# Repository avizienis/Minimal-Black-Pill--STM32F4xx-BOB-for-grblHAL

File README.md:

# Minimal Black Pill (STM32F4xx) BOB for grblHAL 
Single layer breakout board for the popular Black Pill (*NOT Blue Pill*). Features 4 axes, 5V outputs, optoisolated inputs.

Firmware: [grblHAL](https://github.com/terjeio/grblHAL)

The goal of this project was to replace a classical Grbl setup on an Arduino Uno/Nano, with minimal effort and minimal features (which is enough for most hobby machines anyway).
All inputs are mapped to one side of the board, all outputs (except spindle PWM) are on the other. 
This allows for a very clean single sided design and is very suitable milling, UV exposing or even toner transfer methods.
The only critical requirements for manufacturing - minimal separation between traces is 0.2mm.

## Feb 2021 Initial release
  * 4 Axis outputs
  * 10 5V buffered outputs (XYZA step/dir outputs, single source-multiple buffered outputs enable, spindle PWM and enable, mist, flood)  
  * 8 Opto-isolated inputs (mapped to XYZ limits, probe, halt, pause, start, safety door)
  * External supply connectors. Can be powered by USB, external 5V or external 12V-24V (depending on the Vreg). 
  * All I/O done on 3.5mm pitch connectors.

## Notes

### Vreg can be a simple 7805 or as in my implementation (also see images folder) - a tiny DC-DC converter. The latter happily accepts up to 24V input.

### This is only tested on genuine [WeAct Black Pill V3](https://github.com/WeActTC/MiniF4-STM32F4x1).
Other/older versions of the board can have slightly different mappings.
Also I've read that blocking USB power diodes are not present on some older variants of the board.
If so, when using external supply microcontroller's 5V lines should not be connected to the main board.

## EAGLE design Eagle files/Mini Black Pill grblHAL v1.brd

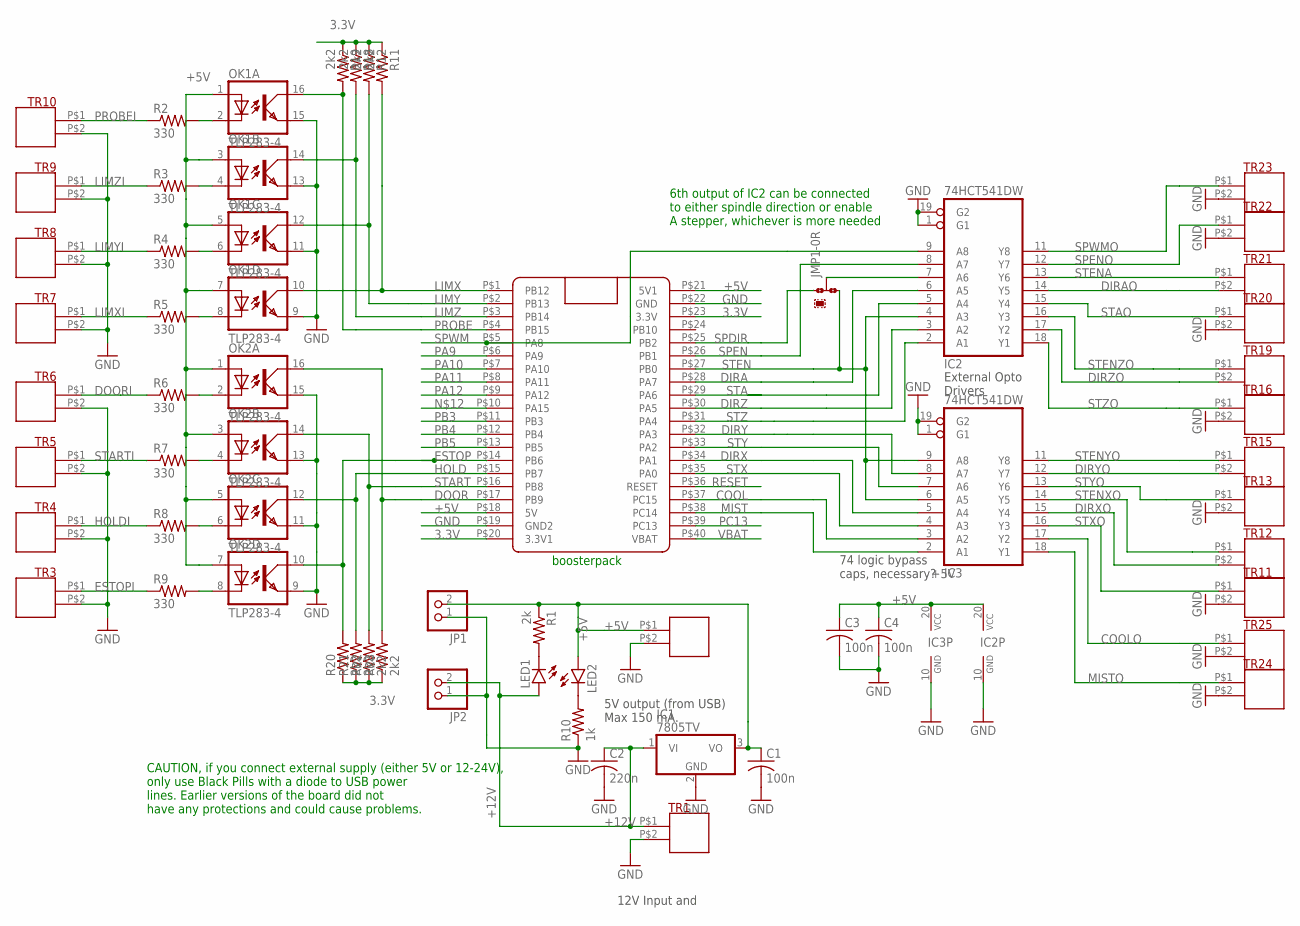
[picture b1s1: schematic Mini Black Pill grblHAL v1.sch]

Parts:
C1, C3, C4: 100n; C0805
C2: 220n; C0805
IC1: 7805TV; TO220V
IC2, IC3: 74HCT541DW; SO20W
JMP1: 0R-JUMPA; A0R-JMP
JP1, JP2: PINHD-1X2; 1X02
LED1, LED2: LED3MM
OK1, OK2: TLP283-4; MINI-FLAT-16
R1: 2k; R0805
R2, R3, R4, R5, R6, R7, R8, R9: 330; R0805
R10: 1k; R0805
R11, R12, R18, R19, R20, R21, R22, R23: 2k2; R0805
TR1, TR2, TR3, TR4, TR5, TR6, TR7, TR8, TR9, TR10, TR11, TR12, TR13, TR15, TR16, TR19, TR20, TR21, TR22, TR23, TR24, TR25: T35-2
U$2: BLACK_PILL; BLUE_PILL

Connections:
3.3V: R11.1, R12.1, R18.1, R19.1, R20.1, R21.1, R22.1, R23.1, U$2.P$20 (3.3V1), U$2.P$23 (3.3V)
+5V: C1.1, C3.1, C4.1, IC1.3 (VO), IC2.20 (VCC), IC3.20 (VCC), JP1.2, LED2.A, OK1.1 (A), OK1.3 (A), OK1.5 (A), OK1.7 (A), OK2.1 (A), OK2.3 (A), OK2.5 (A), OK2.7 (A), R1.1, TR2.P$1, U$2.P$18 (5V), U$2.P$21 (5V1)
+12V: C2.1, IC1.1 (VI), JP2.2, LED1.A, TR1.P$1
COOL: IC3.3 (A2), U$2.P$37 (PC15)
COOLO: IC3.17 (Y2), TR25.P$1
DIRA: IC2.6 (A5), U$2.P$28 (PA7)
DIRAO: IC2.14 (Y5), TR21.P$2
DIRX: IC3.5 (A4), U$2.P$34 (PA1)
DIRXO: IC3.15 (Y4), TR12.P$2
DIRY: IC3.8 (A7), U$2.P$32 (PA3)
DIRYO: IC3.12 (Y7), TR15.P$2
DIRZ: IC2.3 (A2), U$2.P$30 (PA5)
DIRZO: IC2.17 (Y2), TR19.P$2
DOOR: OK2.16 (COL), R23.2, U$2.P$17 (PB9)
DOORI: R6.1, TR6.P$1
ESTOP: OK2.10 (COL), R20.2, U$2.P$14 (PB6)
ESTOPI: R9.1, TR3.P$1
GND: C1.2, C2.2, C3.2, C4.2, IC1.2 (GND), IC2.1 (G1), IC2.10 (GND), IC2.19 (G2), IC3.1 (G1), IC3.10 (GND), IC3.19 (G2), JP1.1, JP2.1, OK1.9 (EMIT), OK1.11 (EMIT), OK1.13 (EMIT), OK1.15 (EMIT), OK2.9 (EMIT), OK2.11 (EMIT), OK2.13 (EMIT), OK2.15 (EMIT), R10.1, TR1.P$2, TR2.P$2, TR3.P$2, TR4.P$2, TR5.P$2, TR6.P$2, TR7.P$2, TR8.P$2, TR9.P$2, TR10.P$2, TR11.P$2, TR13.P$2, TR16.P$2, TR20.P$2, TR22.P$2, TR23.P$2, TR24.P$2, TR25.P$2, U$2.P$19 (GND2), U$2.P$22 (GND)
HOLD: OK2.12 (COL), R21.2, U$2.P$15 (PB7)
HOLDI: R8.1, TR4.P$1
LIMX: OK1.10 (COL), R11.2, U$2.P$1 (PB12)
LIMXI: R5.1, TR7.P$1
LIMY: OK1.12 (COL), R12.2, U$2.P$2 (PB13)
LIMYI: R4.1, TR8.P$1
LIMZ: OK1.14 (COL), R18.2, U$2.P$3 (PB14)
LIMZI: R3.1, TR9.P$1
MIST: IC3.2 (A1), U$2.P$38 (PC14)
MISTO: IC3.18 (Y1), TR24.P$1
unnamed: OK2.2 (C), R6.2
unnamed: LED2.K (C), R10.2
unnamed: OK2.4 (C), R7.2
unnamed: LED1.K (C), R1.2
unnamed: OK2.6 (C), R8.2
unnamed: OK1.8 (C), R5.2
unnamed: OK1.6 (C), R4.2
unnamed: OK1.4 (C), R3.2
unnamed: OK1.2 (C), R2.2
unnamed: OK2.8 (C), R9.2
unnamed: IC2.7 (A6), JMP1.2
PA9: U$2.P$6 (PA9)
PA10: U$2.P$7 (PA10)
PA11: U$2.P$8 (PA11)
PA12: U$2.P$9 (PA12)
PB3: U$2.P$11 (PB3)
PB4: U$2.P$12 (PB4)
PB5: U$2.P$13 (PB5)
PC13: U$2.P$39 (PC13)
PROBE: OK1.16 (COL), R19.2, U$2.P$4 (PB15)
PROBEI: R2.1, TR10.P$1
RESET: U$2.P$36 (RESET)
SPDIR: JMP1.1, U$2.P$25 (PB2)
SPEN: IC2.8 (A7), U$2.P$26 (PB1)
SPENO: IC2.12 (Y7), TR22.P$1
SPWM: IC2.9 (A8), U$2.P$5 (PA8)
SPWMO: IC2.11 (Y8), TR23.P$1
STA: IC2.5 (A4), U$2.P$29 (PA6)
STAO: IC2.15 (Y4), TR20.P$1
START: OK2.14 (COL), R22.2, U$2.P$16 (PB8)
STARTI: R7.1, TR5.P$1
STEN: IC2.4 (A3), IC3.6 (A5), IC3.9 (A8), JMP1.3, U$2.P$27 (PB0)
STENA: IC2.13 (Y6), TR21.P$1
STENXO: IC3.14 (Y5), TR12.P$1
STENYO: IC3.11 (Y8), TR15.P$1
STENZO: IC2.16 (Y3), TR19.P$1
STX: IC3.4 (A3), U$2.P$35 (PA0)
STXO: IC3.16 (Y3), TR11.P$1
STY: IC3.7 (A6), U$2.P$33 (PA2)
STYO: IC3.13 (Y6), TR13.P$1
STZ: IC2.2 (A1), U$2.P$31 (PA4)
STZO: IC2.18 (Y1), TR16.P$1
VBAT: U$2.P$40 (VBAT)

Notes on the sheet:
External Opto Drivers
74 logic bypass caps, necessary?
boosterpack
5V output (from USB) Max 150 mA.
12V Input and
6th output of IC2 can be connected to either spindle direction or enable A stepper, whichever is more needed
CAUTION, if you connect external supply (either 5V or 12-24V), only use Black Pills with a diode to USB power lines. Earlier versions of the board did not have any protections and could cause problems.

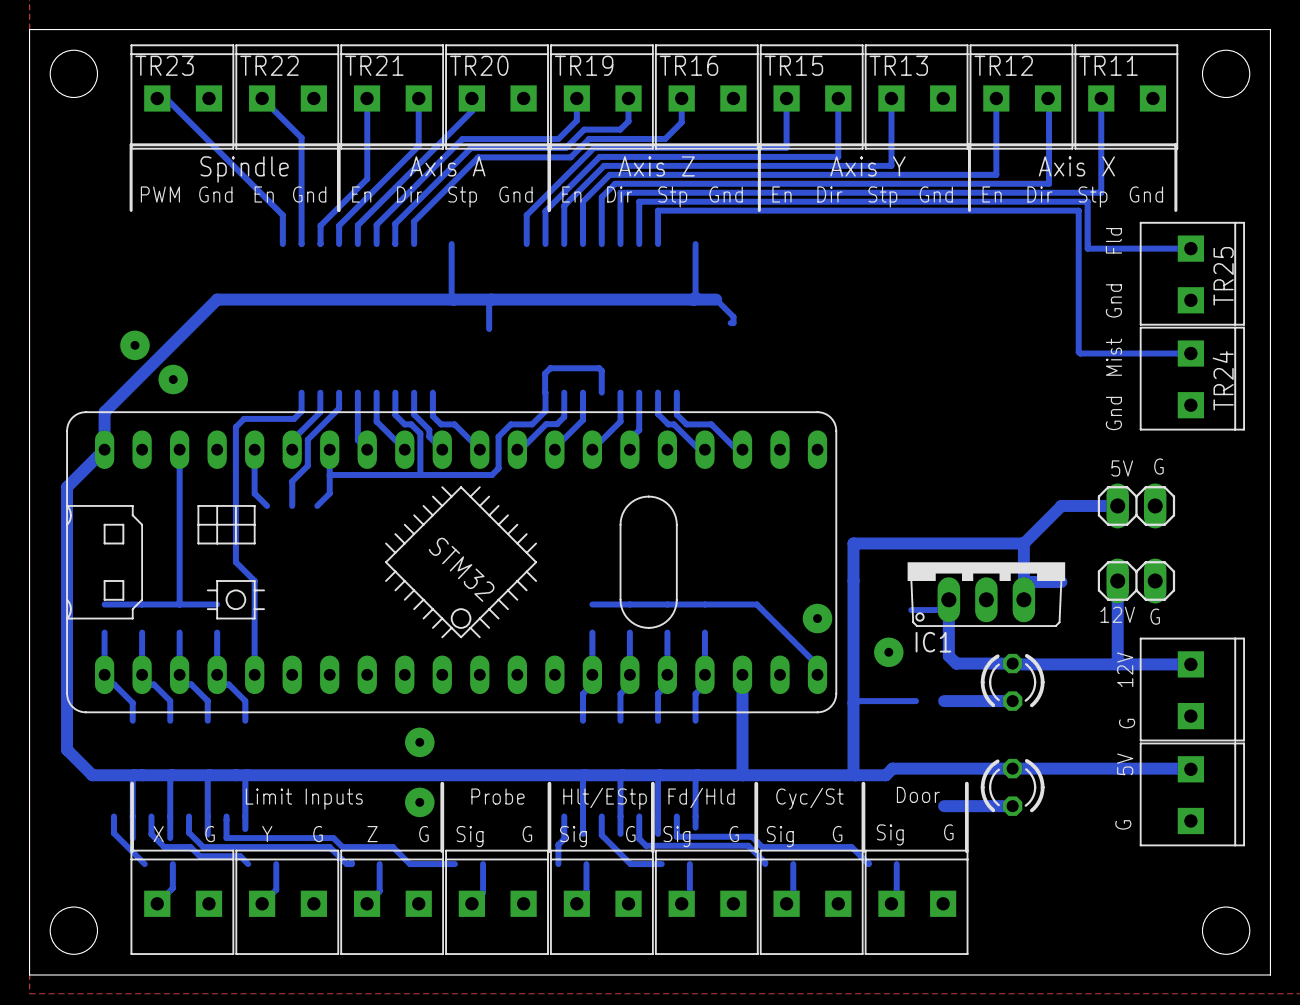
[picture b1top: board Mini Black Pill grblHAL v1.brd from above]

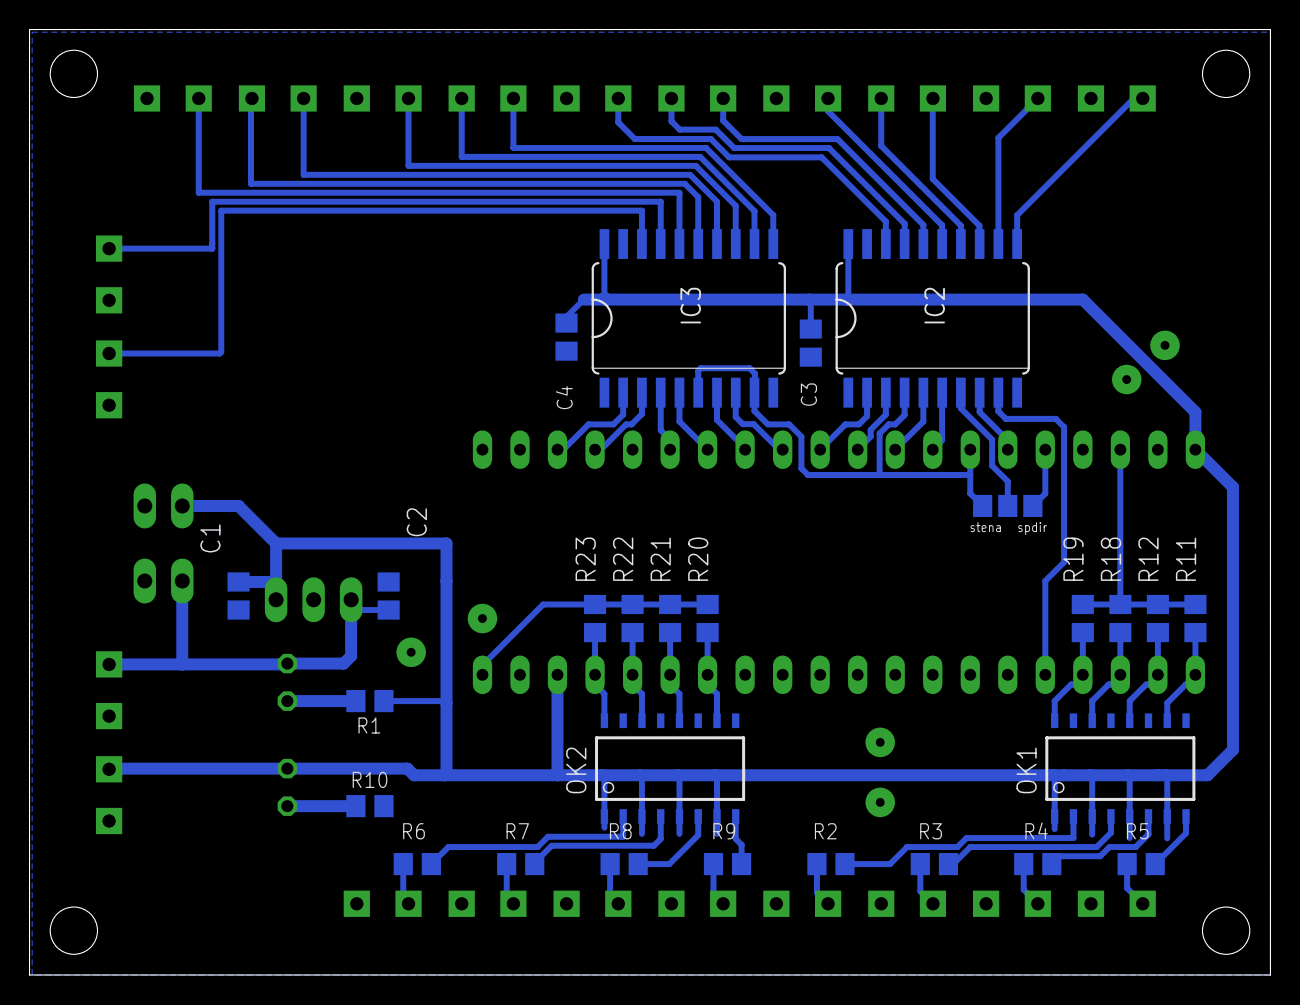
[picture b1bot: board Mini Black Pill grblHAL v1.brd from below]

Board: 2 copper layers, 84.0 x 64.0 mm, 55 parts (27 on the bottom side), 61 nets.

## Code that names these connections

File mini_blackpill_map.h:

/*
  cnc_boosterpack_map.h - driver code for STM32F4xx processor (on Blackpill board)

  Part of GrblHAL

  Copyright (c) 2020 Terje Io

  Grbl is free software: you can redistribute it and/or modify
  it under the terms of the GNU General Public License as published by
  the Free Software Foundation, either version 3 of the License, or
  (at your option) any later version.

  Grbl is distributed in the hope that it will be useful,
  but WITHOUT ANY WARRANTY; without even the implied warranty of
  MERCHANTABILITY or FITNESS FOR A PARTICULAR PURPOSE.  See the
  GNU General Public License for more details.

  You should have received a copy of the GNU General Public License
  along with Grbl.  If not, see <http://www.gnu.org/licenses/>.
*/

#define BOARD_NAME "Minimal BlackPill grblHAL"

#ifdef EEPROM_ENABLE
#undef EEPROM_ENABLE
#endif

#ifdef CNC_BLACKPILL
#undef CNC_BLACKPILL
#endif

#define CNC_BLACKPILL 1
#define EEPROM_ENABLE   0 // Disabled for now for BlackPill - pin differences... // Only change if BoosterPack does not have EEPROM mounted

// Define step pulse output pins.
#define STEP_PORT       GPIOA
#define X_STEP_PIN      0
#define Y_STEP_PIN      2
#define Z_STEP_PIN      4
#define X_STEP_BIT      (1<<X_STEP_PIN)
#define Y_STEP_BIT      (1<<Y_STEP_PIN)
#define Z_STEP_BIT      (1<<Z_STEP_PIN)
#if N_AXIS > 3
#define A_STEP_PIN      6
#define A_STEP_BIT      (1<<A_STEP_PIN)
#define STEP_MASK       (X_STEP_BIT|Y_STEP_BIT|Z_STEP_BIT|A_STEP_BIT) // All step bits
#else
#define STEP_MASK       (X_STEP_BIT|Y_STEP_BIT|Z_STEP_BIT) // All step bits
#endif
#define STEP_OUTMODE    GPIO_MAP

// Define step direction output pins.
#define DIRECTION_PORT      GPIOA
#define X_DIRECTION_PIN     1
#define Y_DIRECTION_PIN     3
#define Z_DIRECTION_PIN     5
#define X_DIRECTION_BIT     (1<<X_DIRECTION_PIN)
#define Y_DIRECTION_BIT     (1<<Y_DIRECTION_PIN)
#define Z_DIRECTION_BIT     (1<<Z_DIRECTION_PIN)
#if N_AXIS > 3
#define A_DIRECTION_PIN     7
#define A_DIRECTION_BIT     (1<<A_DIRECTION_PIN)
#define DIRECTION_MASK      (X_DIRECTION_BIT|Y_DIRECTION_BIT|Z_DIRECTION_BIT|A_DIRECTION_BIT) // All direction bits
#else
#define DIRECTION_MASK      (X_DIRECTION_BIT|Y_DIRECTION_BIT|Z_DIRECTION_BIT) // All direction bits
#endif
#define DIRECTION_OUTMODE   GPIO_MAP

// Define stepper driver enable/disable output pin.
#define STEPPERS_DISABLE_PORT   GPIOB
#define STEPPERS_DISABLE_PIN    0
#define STEPPERS_DISABLE_BIT    (1<<STEPPERS_DISABLE_PIN)
#define STEPPERS_DISABLE_MASK   STEPPERS_DISABLE_BIT

// Define homing/hard limit switch input pins.
#define LIMIT_PORT       GPIOB
#define X_LIMIT_PIN      12
#define Y_LIMIT_PIN      13
#define Z_LIMIT_PIN      14
#define X_LIMIT_BIT      (1<<X_LIMIT_PIN)
#define Y_LIMIT_BIT      (1<<Y_LIMIT_PIN)
#define Z_LIMIT_BIT      (1<<Z_LIMIT_PIN)
#if N_AXIS > 3
#define A_LIMIT_PIN      15
#define A_LIMIT_BIT      (1<<A_LIMIT_PIN)
#define LIMIT_MASK       (X_LIMIT_BIT|Y_LIMIT_BIT|Z_LIMIT_BIT|A_LIMIT_BIT) // All limit bits
#else
#define LIMIT_MASK       (X_LIMIT_BIT|Y_LIMIT_BIT|Z_LIMIT_BIT) // All limit bits
#endif
#define LIMIT_INMODE GPIO_SHIFT12

  // Define spindle enable and spindle direction output pins.
#define SPINDLE_ENABLE_PORT         GPIOB
#define SPINDLE_ENABLE_PIN          1
#define SPINDLE_ENABLE_BIT          (1<<SPINDLE_ENABLE_PIN)
#define SPINDLE_DIRECTION_PORT      GPIOB
#define SPINDLE_DIRECTION_PIN       2
#define SPINDLE_DIRECTION_BIT       (1<<SPINDLE_DIRECTION_PIN)

// Define spindle PWM output pin.
#define SPINDLE_PWM_PORT            GPIOA
#define SPINDLE_PWM_PIN             8
#define SPINDLE_PWM_BIT             (1<<SPINDLE_PWM_PIN)

// Define flood and mist coolant enable output pins.
#define COOLANT_FLOOD_PORT          GPIOC
#define COOLANT_FLOOD_PIN           15
#define COOLANT_FLOOD_BIT           (1<<COOLANT_FLOOD_PIN)
#define COOLANT_MIST_PORT           GPIOC
#define COOLANT_MIST_PIN            14
#define COOLANT_MIST_BIT            (1<<COOLANT_MIST_PIN)

// Define user-control controls (cycle start, reset, feed hold) input pins.
#define CONTROL_PORT                GPIOB
#define CONTROL_RESET_PIN           6
#define CONTROL_FEED_HOLD_PIN       7
#define CONTROL_CYCLE_START_PIN     8
#define CONTROL_SAFETY_DOOR_PIN     9
#define CONTROL_INMODE GPIO_SHIFT6

#define CONTROL_RESET_BIT           (1<<CONTROL_RESET_PIN)
#define CONTROL_FEED_HOLD_BIT       (1<<CONTROL_FEED_HOLD_PIN)
#define CONTROL_CYCLE_START_BIT     (1<<CONTROL_CYCLE_START_PIN)
#define CONTROL_SAFETY_DOOR_BIT     (1<<CONTROL_SAFETY_DOOR_PIN)
#define CONTROL_MASK                (CONTROL_RESET_BIT|CONTROL_FEED_HOLD_BIT|CONTROL_CYCLE_START_BIT|CONTROL_SAFETY_DOOR_BIT)

// Define probe switch input pin.
#define PROBE_PORT                  GPIOB
#define PROBE_PIN                   15
#define PROBE_BIT                   (1<<PROBE_PIN)

#if KEYPAD_ENABLE
#error Keypad not supported
#define KEYPAD_PORT                 GPIOB
#define KEYPAD_STROBE_PIN           15
#define KEYPAD_STROBE_BIT           (1<<KEYPAD_STROBE_PIN)
#endif

#if SDCARD_ENABLE
#error SDcard not supported
#define SD_CS_PORT  GPIOA
#define SD_CS_PIN   3
#define SD_CS_BIT   (1<<SD_CS_PIN)
#endif

/* EOF */

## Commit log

2021-02-09 Added schematic
